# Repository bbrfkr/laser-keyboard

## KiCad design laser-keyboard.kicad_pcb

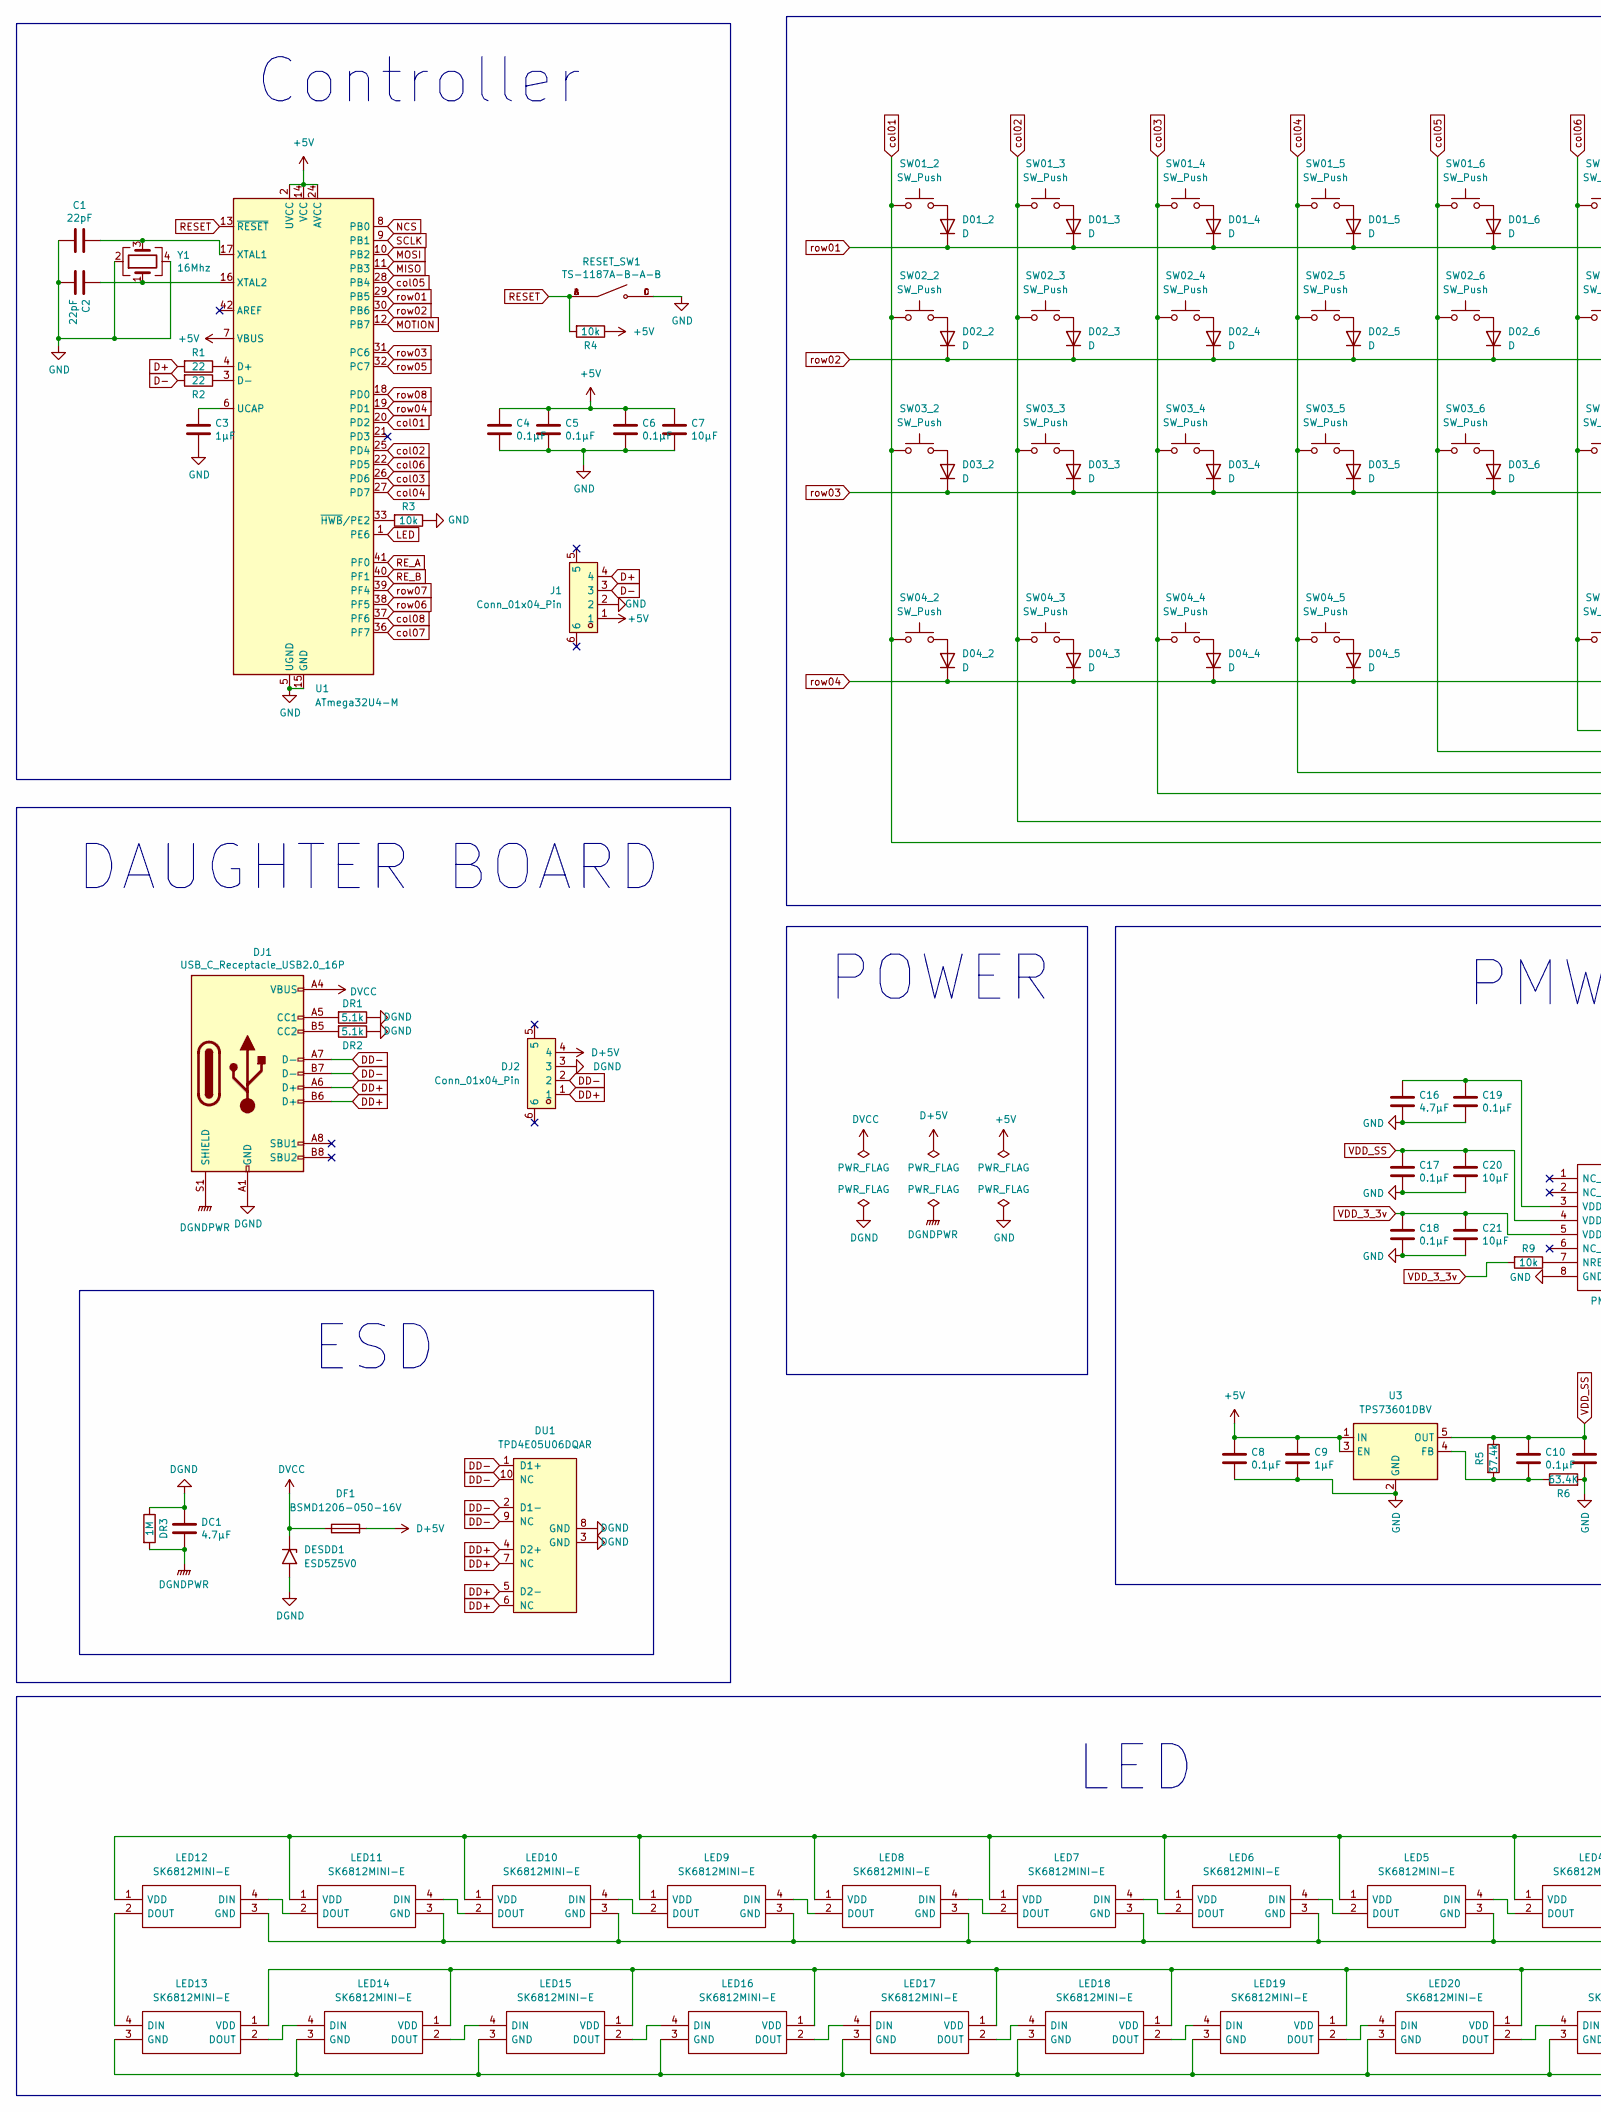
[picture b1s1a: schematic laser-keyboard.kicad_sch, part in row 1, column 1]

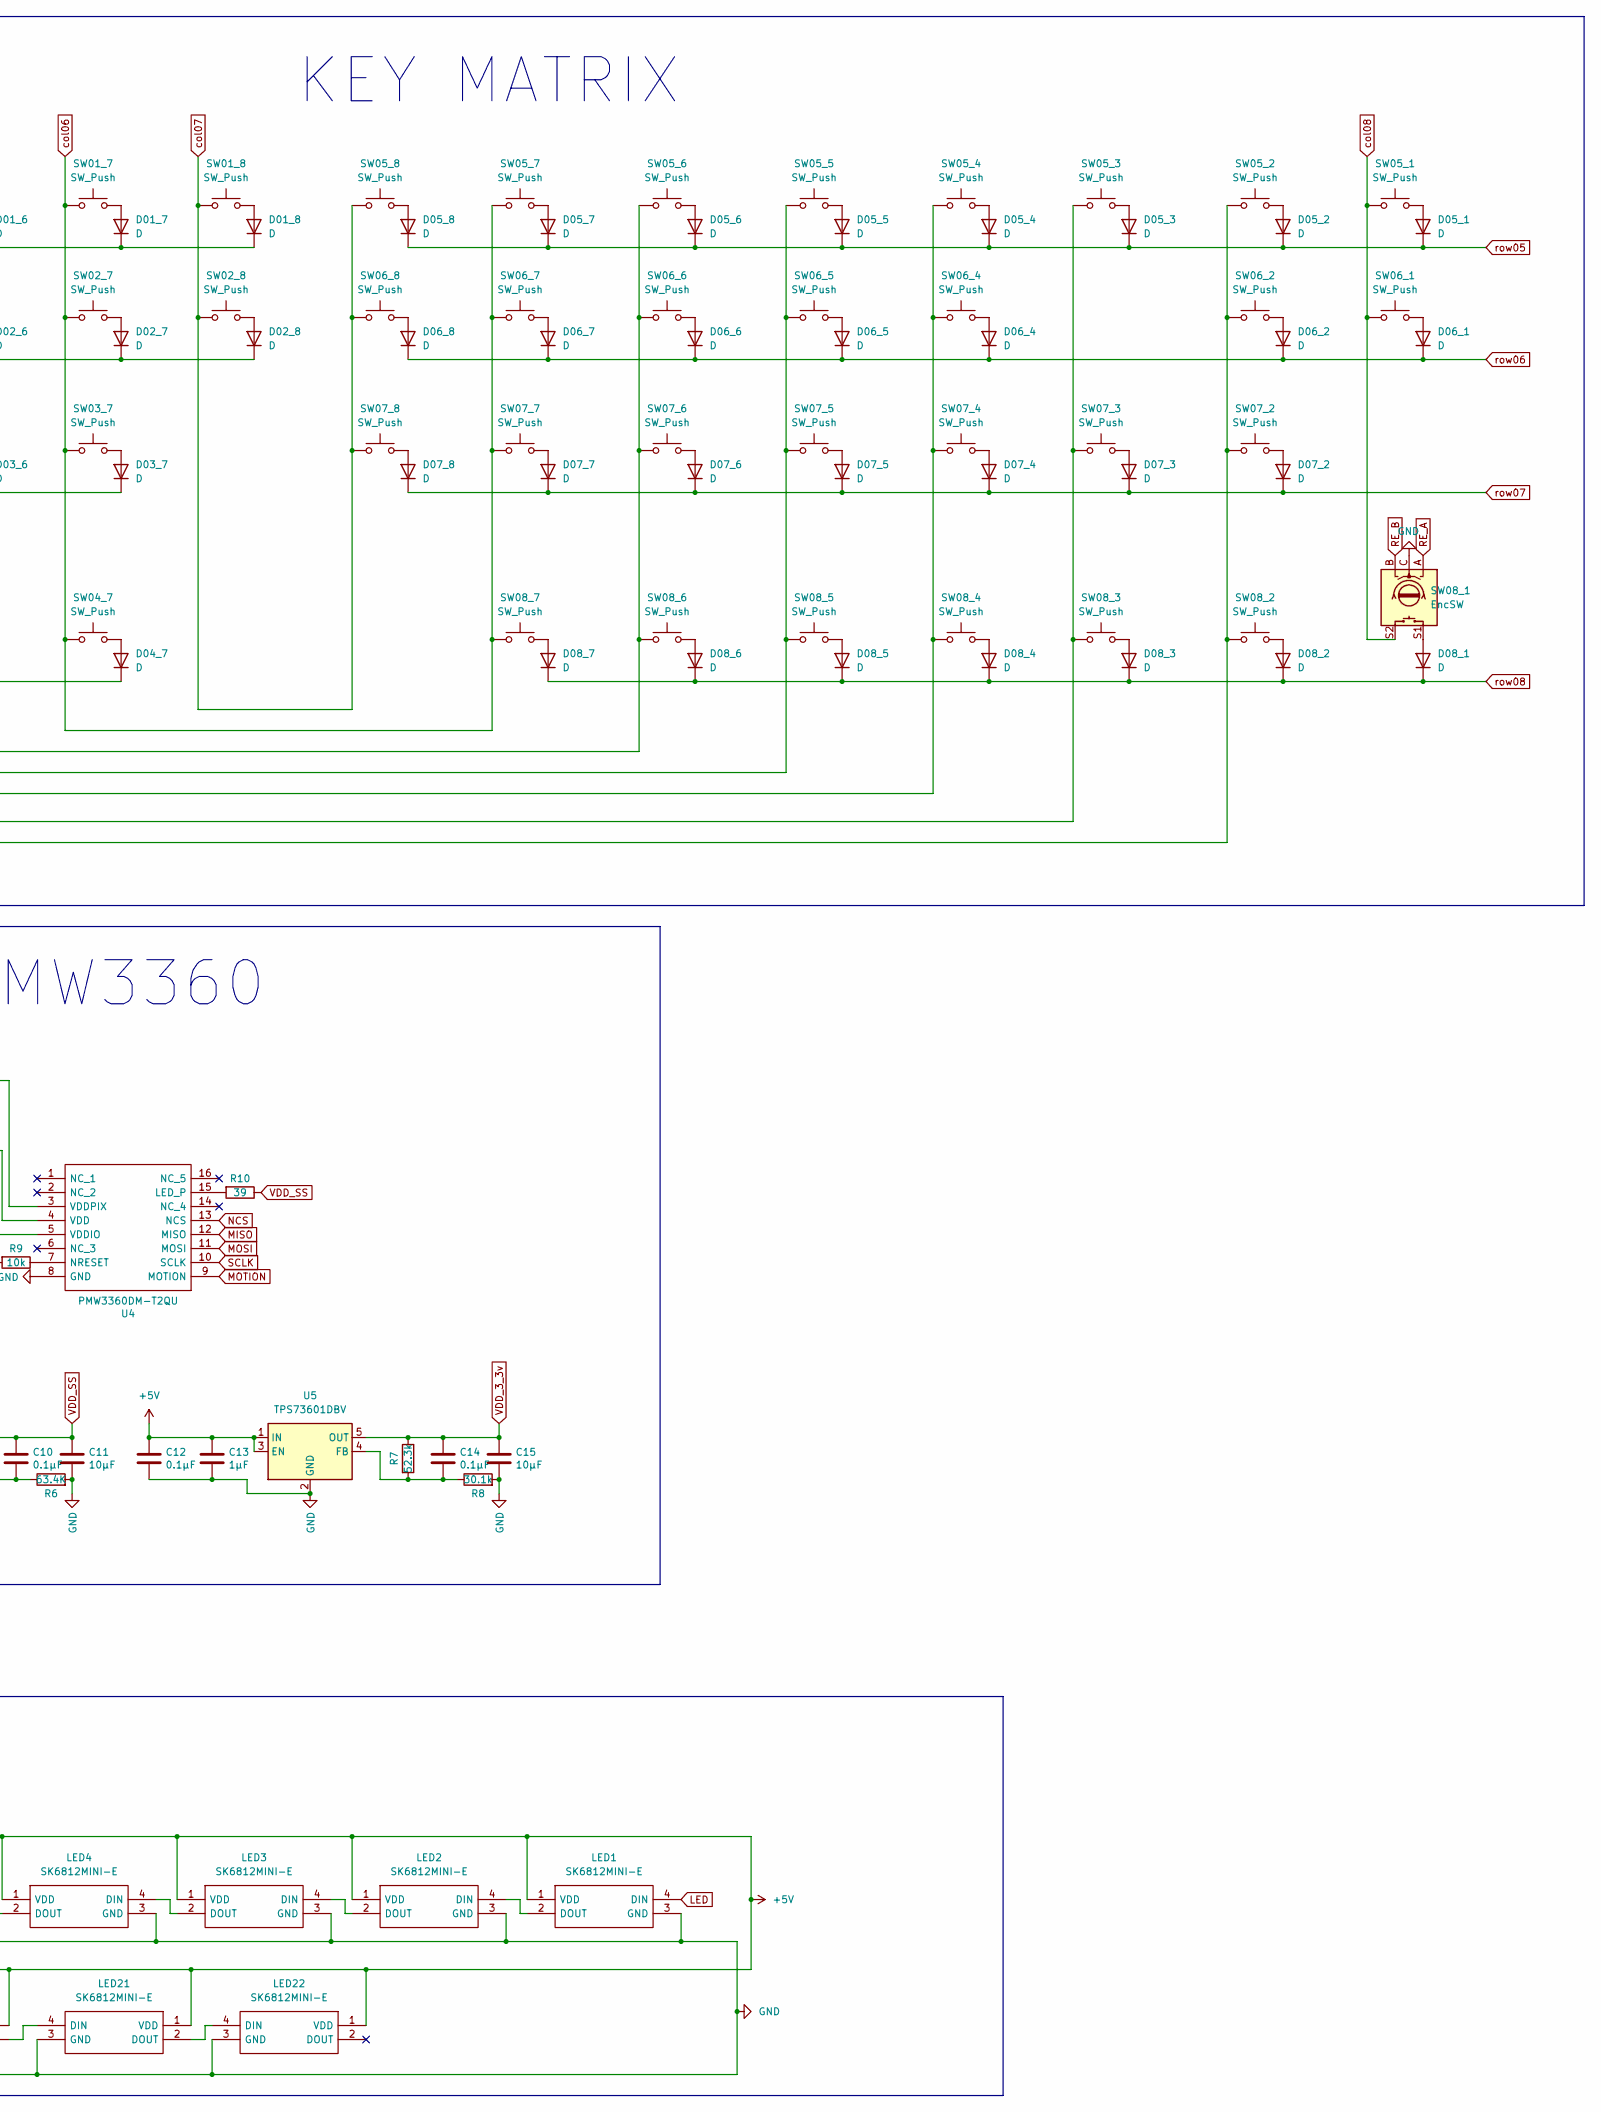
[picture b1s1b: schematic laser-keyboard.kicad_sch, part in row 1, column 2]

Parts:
C1, C2: 22pF; C_1206_3216Metric; LCSC C107174
C3, C9, C13: 1μF; C_1206_3216Metric; LCSC C1848
C4, C5, C6, C8, C10, C12, C14, C17, C18, C19: 0.1μF; C_1206_3216Metric; LCSC C24497
C7, C11, C15, C20, C21: 10μF; C_1206_3216Metric; LCSC C13585
C16: 4.7μF; C_1206_3216Metric; LCSC C29823
D01_2, D01_3, D01_4, D01_5, D01_6, D01_7, D01_8, D02_2, D02_3, D02_4, D02_5, D02_6, D02_7, D02_8, D03_2, D03_3, D03_4, D03_5, D03_6, D03_7, D04_2, D04_3, D04_4, D04_5, D04_7, D05_1, D05_2, D05_3, D05_4, D05_5, D05_6, D05_7, D05_8, D06_1, D06_2, D06_4, D06_5, D06_6, D06_7, D06_8, D07_2, D07_3, D07_4, D07_5, D07_6, D07_7, D07_8, D08_1, D08_2, D08_3, D08_4, D08_5, D08_6, D08_7: D; D_SOD-123-Pretty; LCSC C81598
DC1: 4.7μF; C_1206_3216Metric; LCSC C29823
DESDD1: ESD5Z5V0; D_SOD-523; Manufacturer Part Number ESD5Z5V0; LCSC C502546
DF1: BSMD1206-050-16V; Fuse_1206_3216Metric; Manufacturer Part Number BSMD1206-050-16V; LCSC C883124
DJ1: USB_C_Receptacle_USB2.0_16P; USB_C_Receptacle_HRO_TYPE-C-31-M-12; LCSC C165948
DJ2: Conn_01x04_Pin; FPC-SMD_4P-P1.00_1157-04AU; LCSC Part C2886699
DR1, DR2: 5.1k; R_1206_3216Metric; LCSC C26033
DR3: 1M; R_1206_3216Metric; LCSC C17927
DU1: TPD4E05U06DQAR; USON-10_L2.5-W1.0-P0.50-BL; LCSC C2836386
J1: Conn_01x04_Pin; FPC-SMD_4P-P1.00_1157-04AU; LCSC Part C2886699
LED1, LED2, LED3, LED4, LED5, LED6, LED7, LED8, LED9, LED10, LED11, LED12, LED13, LED14, LED15, LED16, LED17, LED18, LED19, LED20, LED21, LED22: SK6812MINI-E; SK6812MINIE; Manufacturer_Part_Number SK6812MINI-E
R1, R2: 22; R_1206_3216Metric; LCSC C17958
R3, R4, R9: 10k; R_1206_3216Metric; LCSC C1489
R5: 37.4k; R_1206_3216Metric; LCSC C229581
R6: 63.4K; R_1206_3216Metric; LCSC C488931
R7: 52.3k; R_1206_3216Metric; LCSC C488889
R8: 30.1k; R_1206_3216Metric; LCSC C311945
R10: 39; R_1206_3216Metric; LCSC C286655
RESET_SW1: TS-1187A-B-A-B; SW_TS-1187A-B-A-B; PARTREV A0; LCSC C318884
SW01_2, SW05_2: SW_Push; MXOnly-1.5U-Hotswap; LCSC C5156480
SW01_3, SW01_4, SW01_5, SW01_6, SW01_7, SW01_8, SW02_3, SW02_4, SW02_5, SW02_6, SW02_7, SW02_8, SW03_3, SW03_4, SW03_5, SW03_6, SW03_7, SW05_1, SW05_3, SW05_4, SW05_5, SW05_6, SW05_7, SW05_8, SW06_1, SW06_4, SW06_5, SW06_6, SW06_7, SW06_8, SW07_2, SW07_4, SW07_5, SW07_6, SW07_7, SW07_8, SW08_2, SW08_3, SW08_4: SW_Push; MXOnly-1U-Hotswap; LCSC C5156480
SW02_2, SW07_3: SW_Push; MXOnly-1.75U-Hotswap; LCSC C5156480
SW03_2, SW06_2: SW_Push; MXOnly-2.25U-Hotswap; LCSC C5156480
SW04_2, SW04_3, SW04_4, SW04_7, SW08_5, SW08_6: SW_Push; MXOnly-1.25U-Hotswap; LCSC C5156480
SW04_5: SW_Push; MXOnly-2.25U-Hotswap-ReversedStabilizers; LCSC C5156480
SW08_1: EncSW; RotaryEncoder_Alps_EC12E-Switch_Vertical_H20mm
SW08_7: SW_Push; MXOnly-2.75U-Hotswap-ReversedStabilizers; LCSC C5156480
U1: ATmega32U4-M; QFN-44-1EP_7x7mm_P0.5mm_EP5.2x5.2mm; LCSC C112161
U3, U5: TPS73601DBV; SOT-23-5; LCSC C59200
U4: PMW3360DM-T2QU; PMW3360; Manufacturer_Part_Number PMW3360DM-T2QU
Y1: 16Mhz; OSC-SMD_4P-L3.2-W2.5-BL; LCSC C13738

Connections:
+5V: C4.1, C5.1, C6.1, C7.1, C8.1, C9.1, C12.1, C13.1, J1.1, LED1.1 (VDD), LED2.1 (VDD), LED3.1 (VDD), LED4.1 (VDD), LED5.1 (VDD), LED6.1 (VDD), LED7.1 (VDD), LED8.1 (VDD), LED9.1 (VDD), LED10.1 (VDD), LED11.1 (VDD), LED12.1 (VDD), LED13.1 (VDD), LED14.1 (VDD), LED15.1 (VDD), LED16.1 (VDD), LED17.1 (VDD), LED18.1 (VDD), LED19.1 (VDD), LED20.1 (VDD), LED21.1 (VDD), LED22.1 (VDD), R4.1, U1.2 (UVCC), U1.7 (VBUS), U1.14 (VCC), U1.24 (AVCC), U1.34 (VCC), U1.44 (AVCC), U3.1 (IN), U3.3 (EN), U5.1 (IN), U5.3 (EN)
D+: J1.4, R1.2
D+5V: DF1.2, DJ2.4
D-: J1.3, R2.2
DD+: DJ1.A6 (D+), DJ1.B6 (D+), DJ2.1, DU1.4 (D2+), DU1.5 (D2-), DU1.6 (NC), DU1.7 (NC)
DD-: DJ1.A7 (D-), DJ1.B7 (D-), DJ2.2, DU1.1 (D1+), DU1.2 (D1-), DU1.9 (NC), DU1.10 (NC)
DGND: DC1.1, DESDD1.2 (A2), DJ1.A1 (GND), DJ1.A12 (GND), DJ1.B1 (GND), DJ1.B12 (GND), DJ2.3, DR1.1, DR2.1, DR3.1, DU1.3 (GND), DU1.8 (GND)
DGNDPWR: DC1.2, DJ1.S1 (SHIELD), DR3.2
DVCC: DESDD1.1 (A1), DF1.1, DJ1.A4 (VBUS), DJ1.A9 (VBUS), DJ1.B4 (VBUS), DJ1.B9 (VBUS)
GND: C1.1, C2.2, C3.2, C4.2, C5.2, C6.2, C7.2, C8.2, C9.2, C11.2, C12.2, C13.2, C15.2, C16.2, C17.2, C18.2, C19.2, C20.2, C21.2, J1.2, LED1.3 (GND), LED2.3 (GND), LED3.3 (GND), LED4.3 (GND), LED5.3 (GND), LED6.3 (GND), LED7.3 (GND), LED8.3 (GND), LED9.3 (GND), LED10.3 (GND), LED11.3 (GND), LED12.3 (GND), LED13.3 (GND), LED14.3 (GND), LED15.3 (GND), LED16.3 (GND), LED17.3 (GND), LED18.3 (GND), LED19.3 (GND), LED20.3 (GND), LED21.3 (GND), LED22.3 (GND), R3.1, R6.2, R8.2, RESET_SW1.C, RESET_SW1.D, SW08_1.C, U1.5 (UGND), U1.15 (GND), U1.23 (GND), U1.35 (GND), U1.43 (GND), U1.45 (GND), U3.2 (GND), U4.8 (GND), U5.2 (GND), Y1.2, Y1.4
LED: LED1.4 (DIN), U1.1 (PE6)
MISO: U1.11 (PB3), U4.12 (MISO)
MOSI: U1.10 (PB2), U4.11 (MOSI)
MOTION: U1.12 (PB7), U4.9 (MOTION)
NCS: U1.8 (PB0), U4.13 (NCS)
unnamed: D01_2.2 (A), SW01_2.2
unnamed: D01_3.2 (A), SW01_3.2
unnamed: D01_4.2 (A), SW01_4.2
unnamed: D01_5.2 (A), SW01_5.2
unnamed: D01_6.2 (A), SW01_6.2
unnamed: D01_7.2 (A), SW01_7.2
unnamed: D01_8.2 (A), SW01_8.2
unnamed: D02_2.2 (A), SW02_2.2
unnamed: D02_3.2 (A), SW02_3.2
unnamed: D02_4.2 (A), SW02_4.2
unnamed: D02_5.2 (A), SW02_5.2
unnamed: D02_6.2 (A), SW02_6.2
unnamed: D02_7.2 (A), SW02_7.2
unnamed: D02_8.2 (A), SW02_8.2
unnamed: D03_2.2 (A), SW03_2.2
unnamed: D03_3.2 (A), SW03_3.2
unnamed: D03_4.2 (A), SW03_4.2
unnamed: D03_5.2 (A), SW03_5.2
unnamed: D03_6.2 (A), SW03_6.2
unnamed: D03_7.2 (A), SW03_7.2
unnamed: D04_2.2 (A), SW04_2.2
unnamed: D04_3.2 (A), SW04_3.2
unnamed: D04_4.2 (A), SW04_4.2
unnamed: D04_5.2 (A), SW04_5.2
unnamed: D04_7.2 (A), SW04_7.2
unnamed: D05_1.2 (A), SW05_1.2
unnamed: D05_2.2 (A), SW05_2.2
unnamed: D05_3.2 (A), SW05_3.2
unnamed: D05_4.2 (A), SW05_4.2
unnamed: D05_5.2 (A), SW05_5.2
unnamed: D05_6.2 (A), SW05_6.2
unnamed: D05_7.2 (A), SW05_7.2
unnamed: D05_8.2 (A), SW05_8.2
unnamed: D06_1.2 (A), SW06_1.2
unnamed: D06_2.2 (A), SW06_2.2
unnamed: D06_4.2 (A), SW06_4.2
unnamed: D06_5.2 (A), SW06_5.2
unnamed: D06_6.2 (A), SW06_6.2
unnamed: D06_7.2 (A), SW06_7.2
unnamed: D06_8.2 (A), SW06_8.2
unnamed: D07_2.2 (A), SW07_2.2
unnamed: D07_3.2 (A), SW07_3.2
unnamed: D07_4.2 (A), SW07_4.2
unnamed: D07_5.2 (A), SW07_5.2
unnamed: D07_6.2 (A), SW07_6.2
unnamed: D07_7.2 (A), SW07_7.2
unnamed: D07_8.2 (A), SW07_8.2
unnamed: D08_1.2 (A), SW08_1.S1
unnamed: D08_2.2 (A), SW08_2.2
unnamed: D08_3.2 (A), SW08_3.2
unnamed: D08_4.2 (A), SW08_4.2
unnamed: D08_5.2 (A), SW08_5.2
unnamed: D08_6.2 (A), SW08_6.2
unnamed: D08_7.2 (A), SW08_7.2
unnamed: DJ1.A5 (CC1), DR1.2
unnamed: DJ1.B5 (CC2), DR2.2
unnamed: LED1.2 (DOUT), LED2.4 (DIN)
unnamed: LED2.2 (DOUT), LED3.4 (DIN)
unnamed: LED3.2 (DOUT), LED4.4 (DIN)
unnamed: LED4.2 (DOUT), LED5.4 (DIN)
unnamed: LED5.2 (DOUT), LED6.4 (DIN)
unnamed: LED6.2 (DOUT), LED7.4 (DIN)
unnamed: LED7.2 (DOUT), LED8.4 (DIN)
unnamed: LED8.2 (DOUT), LED9.4 (DIN)
unnamed: LED9.2 (DOUT), LED10.4 (DIN)
unnamed: LED10.2 (DOUT), LED11.4 (DIN)
unnamed: LED11.2 (DOUT), LED12.4 (DIN)
unnamed: LED12.2 (DOUT), LED13.4 (DIN)
unnamed: LED13.2 (DOUT), LED14.4 (DIN)
unnamed: LED14.2 (DOUT), LED15.4 (DIN)
unnamed: LED15.2 (DOUT), LED16.4 (DIN)
unnamed: LED16.2 (DOUT), LED17.4 (DIN)
unnamed: LED17.2 (DOUT), LED18.4 (DIN)
unnamed: LED18.2 (DOUT), LED19.4 (DIN)
unnamed: LED19.2 (DOUT), LED20.4 (DIN)
unnamed: LED20.2 (DOUT), LED21.4 (DIN)
unnamed: LED21.2 (DOUT), LED22.4 (DIN)
unnamed: R1.1, U1.4 (D+)
unnamed: R2.1, U1.3 (D-)
unnamed: C3.1, U1.6 (UCAP)
unnamed: C1.2, U1.17 (XTAL1), Y1.3
unnamed: C2.1, U1.16 (XTAL2), Y1.1
unnamed: R3.2, U1.33 (~HWB/PE2)
unnamed: C10.2, R5.2, R6.1, U3.4 (FB)
unnamed: R10.2, U4.15 (LED_P)
unnamed: R9.1, U4.7 (NRESET)
unnamed: C16.1, C19.1, U4.3 (VDDPIX)
unnamed: C14.2, R7.2, R8.1, U5.4 (FB)
RESET: R4.2, RESET_SW1.A, RESET_SW1.B, U1.13 (~RESET)
RE_A: SW08_1.A, U1.41 (PF0)
RE_B: SW08_1.B, U1.40 (PF1)
SCLK: U1.9 (PB1), U4.10 (SCLK)
VDD_3_3v: C14.1, C15.1, C18.1, C21.1, R7.1, R9.2, U4.5 (VDDIO), U5.5 (OUT)
VDD_SS: C10.1, C11.1, C17.1, C20.1, R5.1, R10.1, U3.5 (OUT), U4.4 (VDD)
col01: SW01_2.1, SW02_2.1, SW03_2.1, SW04_2.1, SW05_2.1, SW06_2.1, SW07_2.1, SW08_2.1, U1.20 (PD2)
col02: SW01_3.1, SW02_3.1, SW03_3.1, SW04_3.1, SW05_3.1, SW07_3.1, SW08_3.1, U1.25 (PD4)
col03: SW01_4.1, SW02_4.1, SW03_4.1, SW04_4.1, SW05_4.1, SW06_4.1, SW07_4.1, SW08_4.1, U1.26 (PD6)
col04: SW01_5.1, SW02_5.1, SW03_5.1, SW04_5.1, SW05_5.1, SW06_5.1, SW07_5.1, SW08_5.1, U1.27 (PD7)
col05: SW01_6.1, SW02_6.1, SW03_6.1, SW05_6.1, SW06_6.1, SW07_6.1, SW08_6.1, U1.28 (PB4)
col06: SW01_7.1, SW02_7.1, SW03_7.1, SW04_7.1, SW05_7.1, SW06_7.1, SW07_7.1, SW08_7.1, U1.22 (PD5)
col07: SW01_8.1, SW02_8.1, SW05_8.1, SW06_8.1, SW07_8.1, U1.36 (PF7)
col08: SW05_1.1, SW06_1.1, SW08_1.S2, U1.37 (PF6)
row01: D01_2.1 (K), D01_3.1 (K), D01_4.1 (K), D01_5.1 (K), D01_6.1 (K), D01_7.1 (K), D01_8.1 (K), U1.29 (PB5)
row02: D02_2.1 (K), D02_3.1 (K), D02_4.1 (K), D02_5.1 (K), D02_6.1 (K), D02_7.1 (K), D02_8.1 (K), U1.30 (PB6)
row03: D03_2.1 (K), D03_3.1 (K), D03_4.1 (K), D03_5.1 (K), D03_6.1 (K), D03_7.1 (K), U1.31 (PC6)
row04: D04_2.1 (K), D04_3.1 (K), D04_4.1 (K), D04_5.1 (K), D04_7.1 (K), U1.19 (PD1)
row05: D05_1.1 (K), D05_2.1 (K), D05_3.1 (K), D05_4.1 (K), D05_5.1 (K), D05_6.1 (K), D05_7.1 (K), D05_8.1 (K), U1.32 (PC7)
row06: D06_1.1 (K), D06_2.1 (K), D06_4.1 (K), D06_5.1 (K), D06_6.1 (K), D06_7.1 (K), D06_8.1 (K), U1.38 (PF5)
row07: D07_2.1 (K), D07_3.1 (K), D07_4.1 (K), D07_5.1 (K), D07_6.1 (K), D07_7.1 (K), D07_8.1 (K), U1.39 (PF4)
row08: D08_1.1 (K), D08_2.1 (K), D08_3.1 (K), D08_4.1 (K), D08_5.1 (K), D08_6.1 (K), D08_7.1 (K), U1.18 (PD0)

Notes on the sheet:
DAUGHTER BOARD
ESD
LED
Controller
KEY MATRIX
PMW3360
POWER

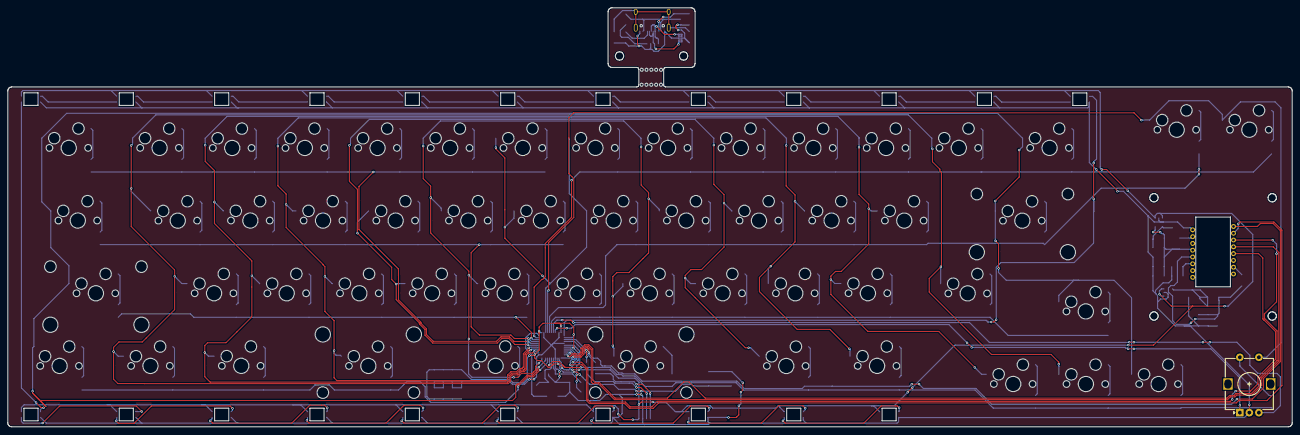
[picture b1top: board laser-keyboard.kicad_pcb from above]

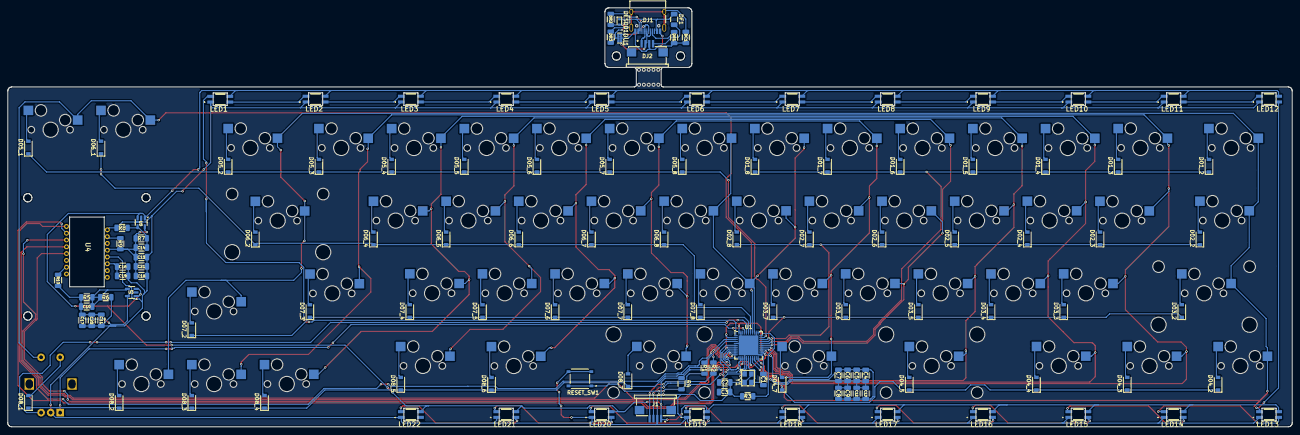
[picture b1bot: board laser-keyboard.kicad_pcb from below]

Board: 2 copper layers, 336.8 x 109.9 mm, 177 parts (101 on the bottom side), 125 nets.

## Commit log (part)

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2025-04-04 pos, bom, gerbers
2025-04-04 init case
2025-04-05 case wip
2025-04-06 bottom case wip
2025-04-06 bottom-case
2025-04-12 modify trackball cup
2025-04-14 bug fix
2025-04-15 firmware and bugfix
2025-05-03 update firmware
2025-05-03 fix mouse button assign
2025-05-04 mod keymap
2025-06-01 v1.0.0
